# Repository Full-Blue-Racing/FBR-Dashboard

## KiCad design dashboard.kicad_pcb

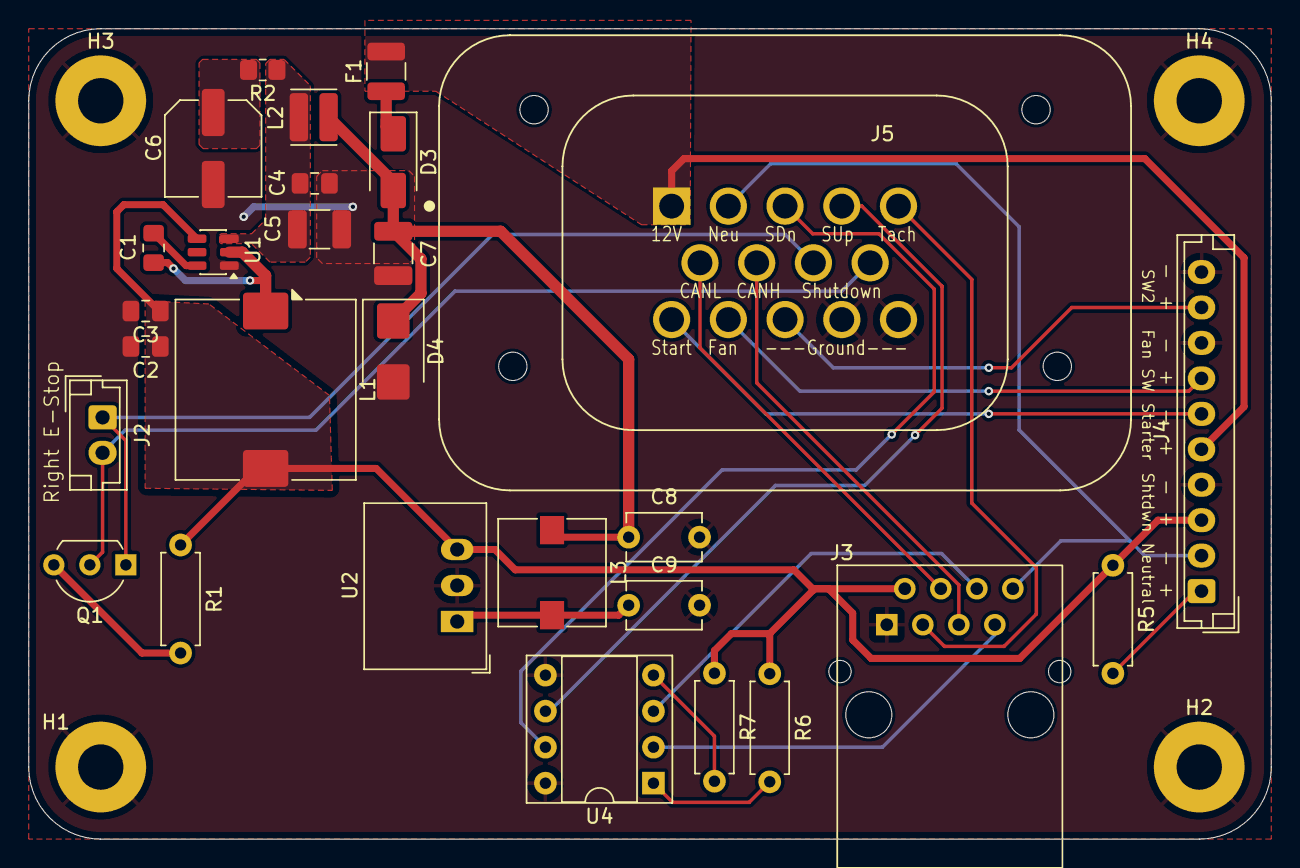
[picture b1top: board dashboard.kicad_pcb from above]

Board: 2 copper layers, 87.6 x 57.2 mm, 33 parts (1 on the bottom side), 27 nets.

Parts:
C1, C3, C4: 100n; C_0805_2012Metric_Pad1.18x1.45mm_HandSolder
C2: 22u; C_0805_2012Metric_Pad1.18x1.45mm_HandSolder
C5: 22u; C_1210_3225Metric_Pad1.33x2.70mm_HandSolder
C6: 56u; C_Elec_6.3x5.8
C7: 10u; C_1210_3225Metric_Pad1.33x2.70mm_HandSolder
C8, C9: 10u; C_Disc_D5.1mm_W3.2mm_P5.00mm
D3: SS34; D_SMA
D4: SMBJ24CA; D_SMB
Dashboard (2026): LOGO; FBR_Logo_.9in
F1: MF-USHT075KX/24-2; L_1210_3225Metric
H1, H2, H3, H4: MountingHole_Pad; MountingHole_3.2mm_M3_Pad
J2: Conn_01x02; JST_EH_B2B-EH-A_1x02_P2.50mm_Vertical
J3: RJ45; RJ45_TE_5557786-1
J4: Conn_01x10; JST_EH_B10B-EH-A_1x10_P2.50mm_Vertical
J5: 776267-1; TE_776262-1
L1: 15u; L_TDK_SLF12575
L2: 560n; L_Wuerth_MAPI-3012
L3: 12u; L_Wuerth_WE-PD-Typ-7345
Q1: 2N7002; TO-92L_Inline_Wide
R1, R5: 120; R_Axial_DIN0207_L6.3mm_D2.5mm_P7.62mm_Horizontal
R2: 100m; R_0805_2012Metric_Pad1.20x1.40mm_HandSolder
R6, R7: 200; R_Axial_DIN0207_L6.3mm_D2.5mm_P7.62mm_Horizontal
U1: TPS542025DDC; SOT-23-6
U2: R-78C5.0-1.0; Converter_DCDC_RECOM_R-78E-0.5_THT
U4: ILD74; DIP-8_W7.62mm_Socket

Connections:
+5V: C2.1, C3.1, J3.2, J4.3, L1.2, R1.1, R5.1, R6.1, R7.1, U1.4 (FB), U2.3 (OUT)
+12V: F1.2, J4.5, J5.1
/CANH: J3.5, J5.7
/CANL: J3.4, J5.6
/Fan_Sig: J4.7, J5.11
/Neutral: J3.8, J4.2, J5.2
/Neutral_LED+: J4.1, R5.2
/PSU+: C7.1, C8.1, D3.2 (A), D4.1 (A1), L2.1, L3.1
/Shift_Dn: J3.7, U4.2
/Shift_Dn_Out: J5.3, U4.7
/Shift_Up: J3.6, U4.3
/Shift_Up_Out: J5.4, U4.6
/Shutdown1: J2.1, J5.8, Q1.1 (G)
/Shutdown2: J2.2, J5.9, Q1.2 (S)
/Spare_Switch_Sig: J4.9, J5.12
/Starter_Sig: J4.6, J5.10
/Tacho: J3.3, J5.5
GND: C2.2, C3.2, C4.2, C5.2, C6.2, C7.2, C8.2, C9.2, D4.2 (A2), H1.1, H2.1, H3.1, H4.1, J3.1, J4.4, J4.8, J4.10, J5.13, J5.14, U1.1 (GND), U2.2 (GND), U4.5, U4.8
unnamed: C6.1, R2.2
unnamed: D3.1 (K), F1.1
unnamed: Q1.3 (D), R1.2
unnamed: R6.2, U4.1
unnamed: R7.2, U4.4
unnamed: C1.1, U1.6 (BOOT)
unnamed: C1.2, L1.1, U1.2 (SW)
unnamed: C4.1, C5.1, L2.2, R2.1, U1.3 (VIN)
unnamed: C9.1, L3.2, U2.1 (IN)

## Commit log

2026-03-29 Rework power supply
2026-03-30 Route PCB
2026-03-30 Add both power supplies
2026-03-31 Add power supply protection
2026-03-31 Revert "Add power supply protection"
    This reverts commit 6c38df0548b9625adbd3b6c051cb9005b09ba150.
2026-03-31 added protection for switching regulator, rerouted PCB
2026-04-01 added thermal vias for TPS54
2026-04-01 Revert "added thermal vias for TPS54"
    This reverts commit a34f3b064daca832ff572b55e7f0ad72ed936012.
2026-04-15 Setup KiCad Action
2026-04-17 Add text and labels
2026-04-17 Formatting
2026-04-17 Fix DRC errors
